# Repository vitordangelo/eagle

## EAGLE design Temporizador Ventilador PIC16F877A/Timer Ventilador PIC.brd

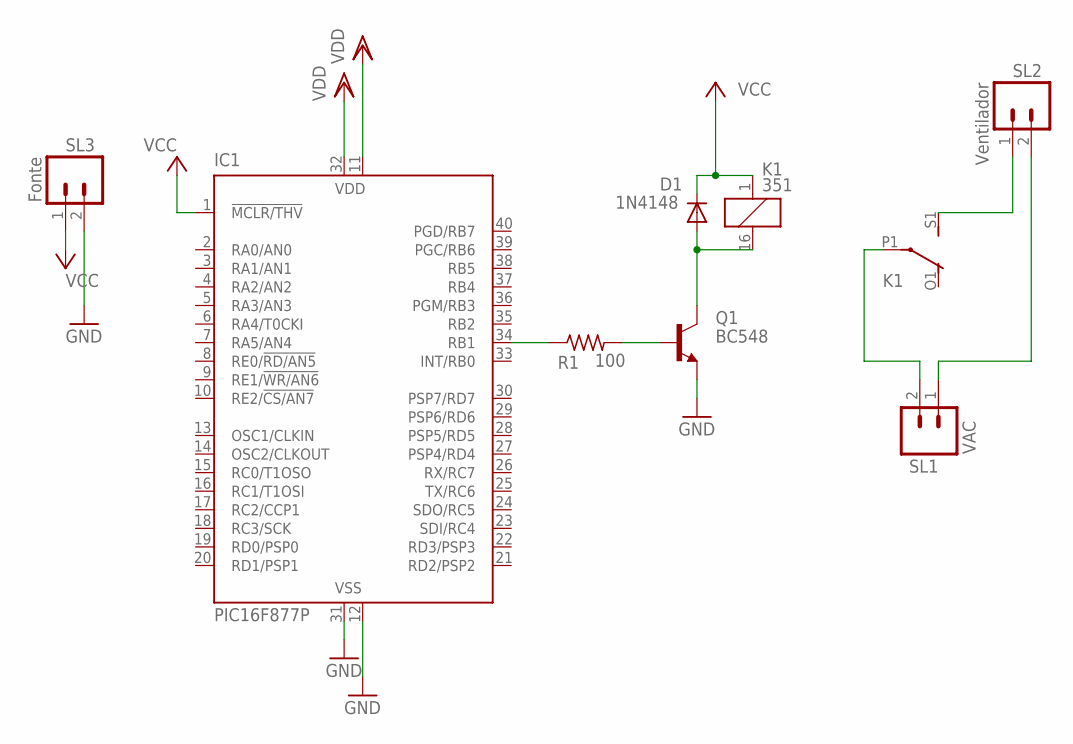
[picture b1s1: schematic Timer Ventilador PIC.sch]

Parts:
D1: 1N4148; DO35-7
IC1: PIC16F877P; DIL40
K1: 351
Q1: BC548; TO92-EBC
R1: 100; 0204/7
SL1: VAC; 02P
SL2: Ventilador; 02P
SL3: Fonte; 02P

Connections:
GND: IC1.12 (VSS), IC1.31 (VSS), Q1.E, SL3.2
unnamed: IC1.34 (RB1), R1.1
unnamed: Q1.B, R1.2
unnamed: K1.P1, SL1.2
unnamed: D1.A, K1.16 (2), Q1.C
unnamed: K1.S1 (S), SL2.1
unnamed: SL1.1, SL2.2
VCC: D1.C, IC1.1 (!MCLR/THV), K1.1, SL3.1
VDD: IC1.11 (VDD), IC1.32 (VDD)

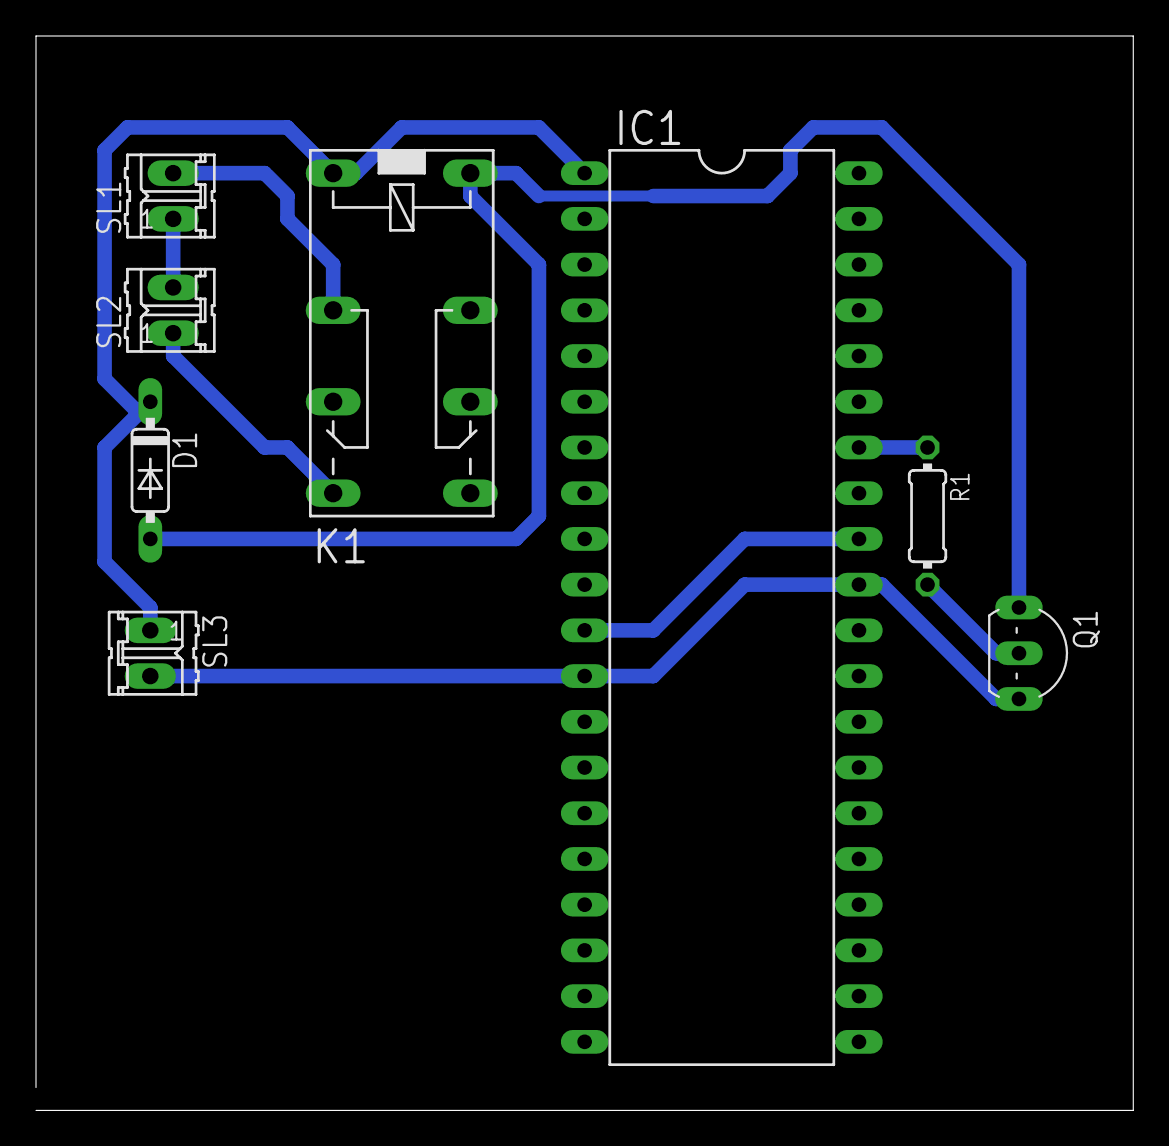
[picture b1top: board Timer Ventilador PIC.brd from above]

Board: 2 copper layers, 61.0 x 59.7 mm, 8 parts (0 on the bottom side), 9 nets.

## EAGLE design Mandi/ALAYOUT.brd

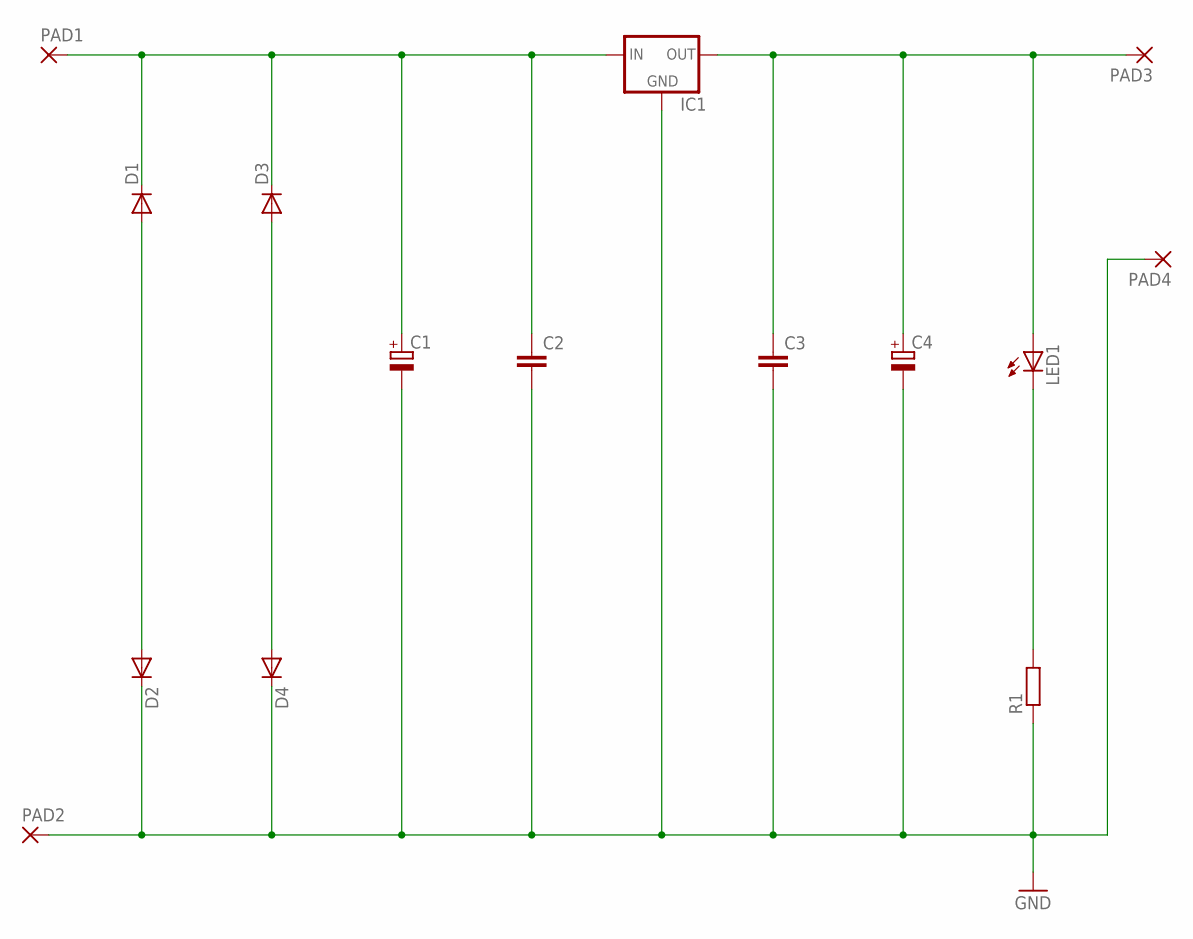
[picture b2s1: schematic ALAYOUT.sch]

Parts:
C1: CPOL-EUE7.5-16; E7,5-16
C2, C3: C-EU050-030X075; C050-030X075
C4: CPOL-EUE5-8.5; E5-8,5
D1, D2, D3, D4: DIODE-DO35-10; DO35-10
IC1: 78XXS
LED1: LED3MM
PAD1, PAD2, PAD3, PAD4: 3,17/1,1
R1: R-EU_0207/10; 0207/10

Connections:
GND: C1.-, C2.2, C3.2, C4.-, D2.C, D4.C, IC1.GND, PAD2.1, PAD4.1, R1.1
unnamed: D3.A, D4.A
unnamed: C1.+, C2.1, D1.C, D3.C, IC1.IN, PAD1.1
unnamed: D1.A, D2.A
unnamed: C3.1, C4.+, IC1.OUT, LED1.A, PAD3.1
unnamed: LED1.K (C), R1.2

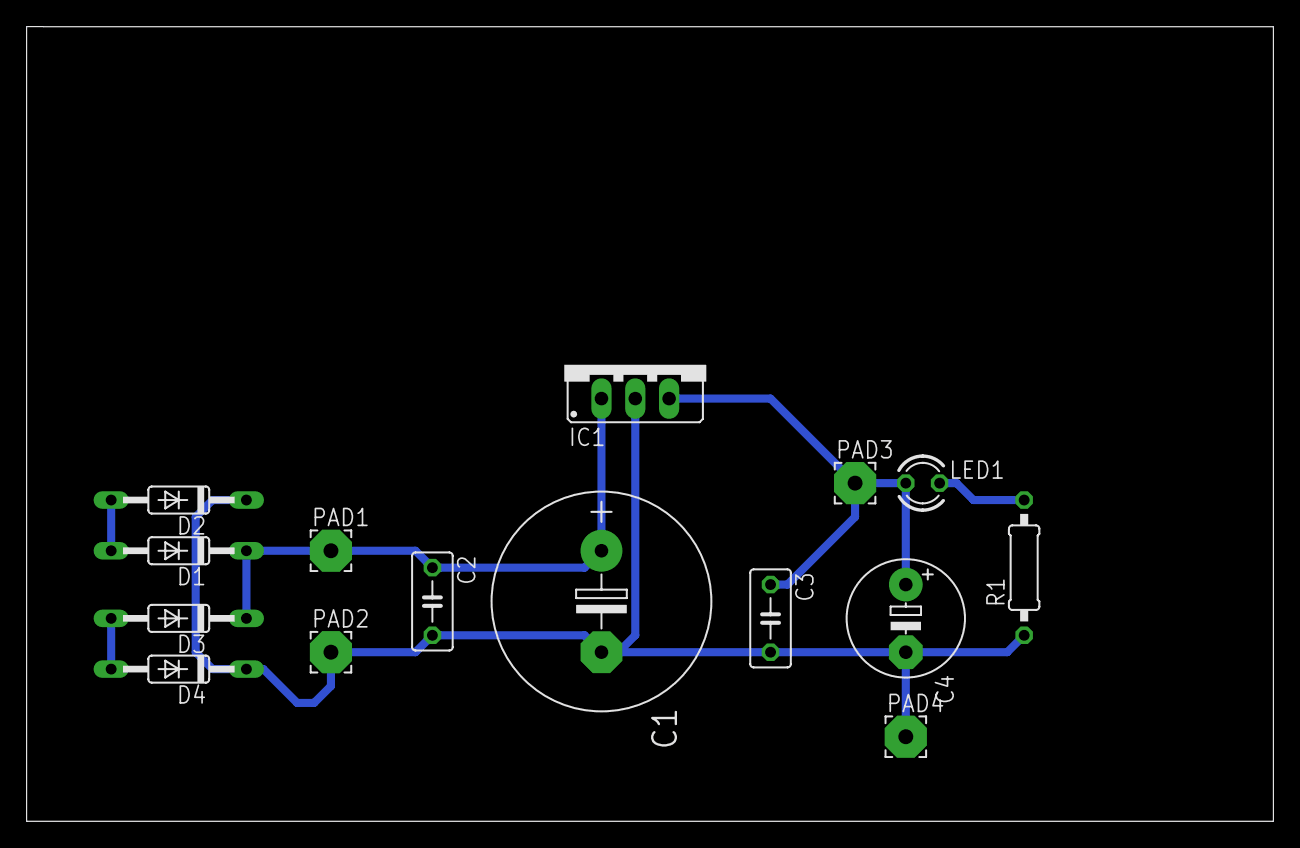
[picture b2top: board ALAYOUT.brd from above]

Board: 2 copper layers, 93.6 x 59.7 mm, 15 parts (0 on the bottom side), 6 nets.

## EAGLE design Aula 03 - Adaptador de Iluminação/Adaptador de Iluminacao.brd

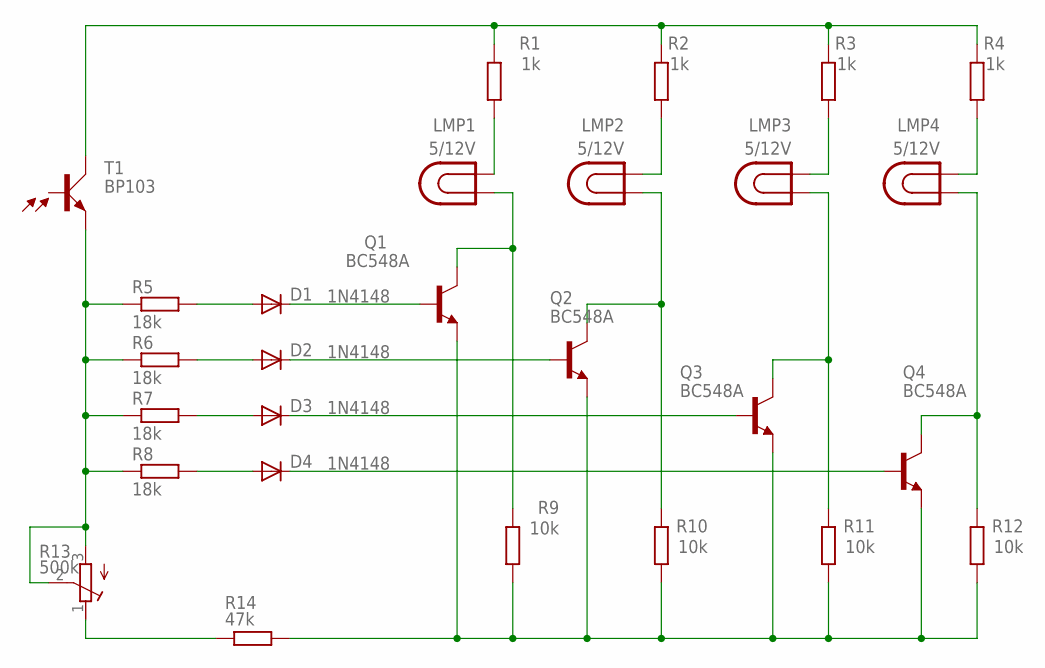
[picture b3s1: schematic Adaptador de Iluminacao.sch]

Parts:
D1, D2, D3, D4: 1N4148; DO35-7
LMP1, LMP2, LMP3, LMP4: 5/12V; LDH-5R
Q1, Q2, Q3, Q4: BC548A; TO92-EBC
R1, R2, R3, R4: 1k; 0207/10
R5, R6, R7, R8: 18k; 0207/10
R9, R10, R11, R12: 10k; 0207/10
R13: 500k; RTRIM43P
R14: 47k; 0207/10
T1: BP103

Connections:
unnamed: R5.1, R6.1, R7.1, R8.1, R13.2 (S), R13.3 (A), T1.E
unnamed: D1.A, R5.2
unnamed: D2.A, R6.2
unnamed: D3.A, R7.2
unnamed: D4.A, R8.2
unnamed: R13.1 (E), R14.1
unnamed: D1.C, Q1.B
unnamed: Q1.E, Q2.E, Q3.E, Q4.E, R9.1, R10.1, R11.1, R12.1, R14.2
unnamed: LMP1.1, Q1.C, R9.2
unnamed: LMP2.1, Q2.C, R10.2
unnamed: LMP1.2, R1.1
unnamed: R1.2, R2.2, R3.2, R4.2, T1.C
unnamed: LMP2.2, R2.1
unnamed: D4.C, Q4.B
unnamed: D2.C, Q2.B
unnamed: D3.C, Q3.B
unnamed: LMP3.1, Q3.C, R11.2
unnamed: LMP4.1, Q4.C, R12.2
unnamed: LMP3.2, R3.1
unnamed: LMP4.2, R4.1

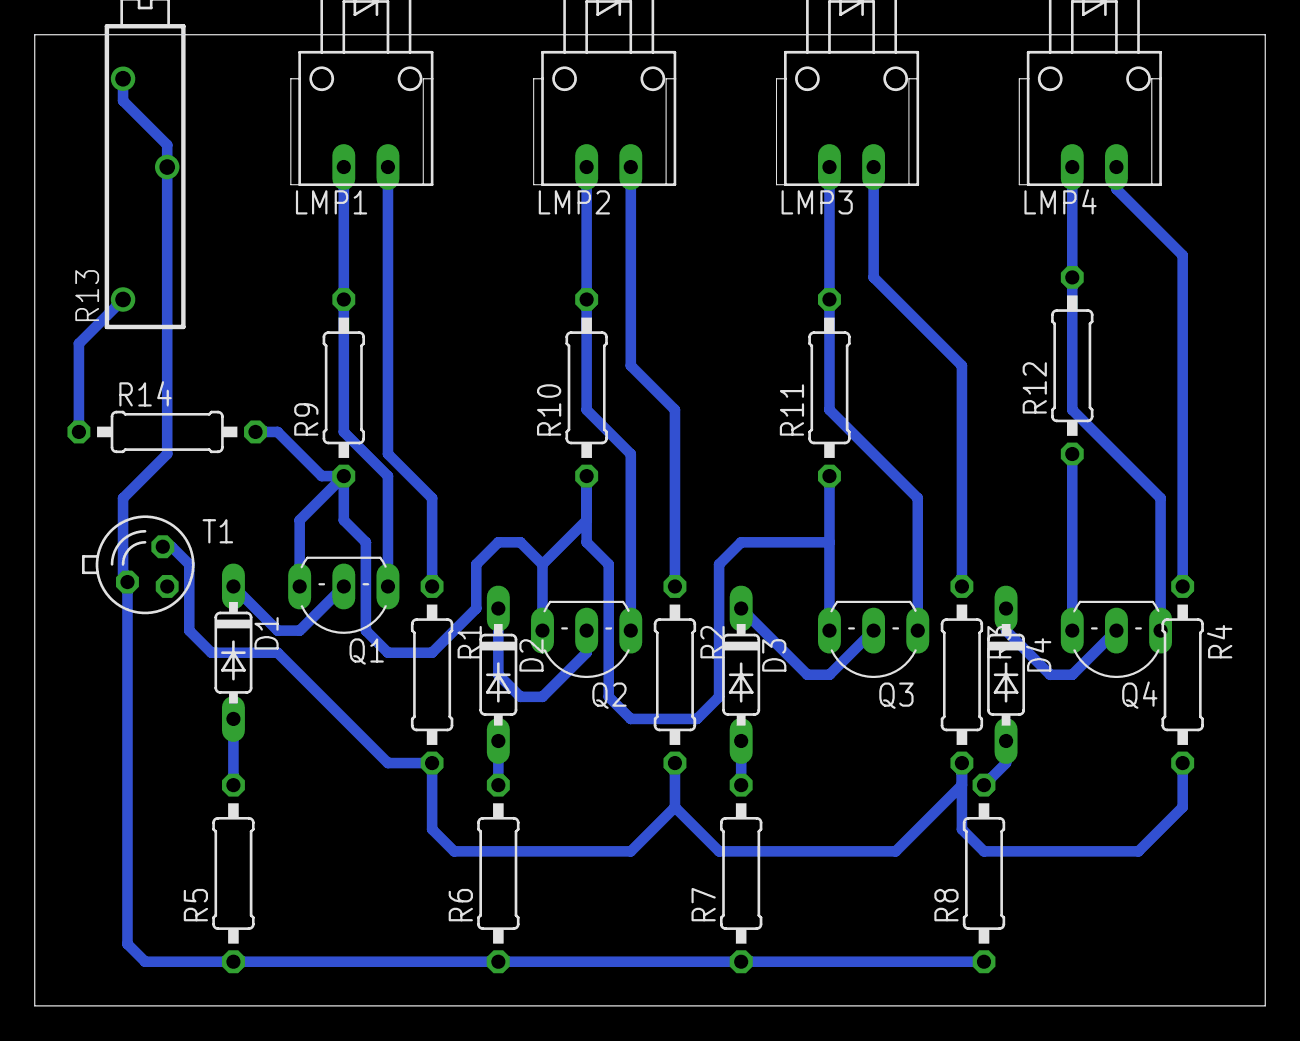
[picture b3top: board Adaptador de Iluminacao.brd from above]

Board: 2 copper layers, 70.8 x 55.9 mm, 27 parts (0 on the bottom side), 20 nets.

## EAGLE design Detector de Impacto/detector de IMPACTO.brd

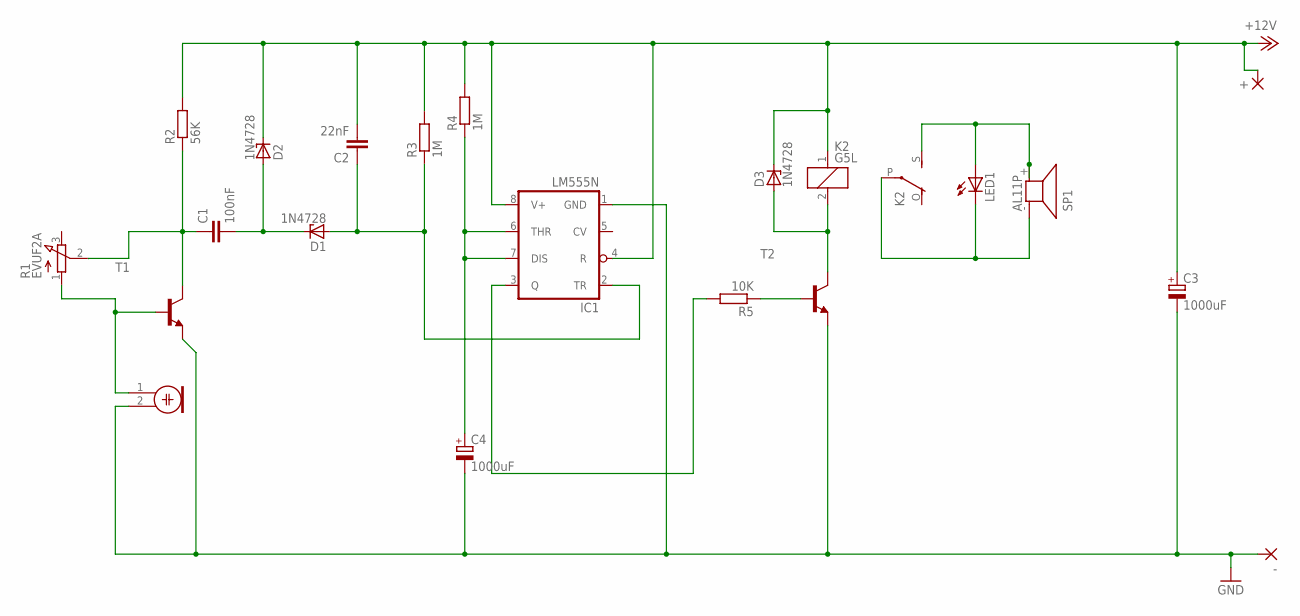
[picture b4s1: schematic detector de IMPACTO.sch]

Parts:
+: 1,6/0,8
-: 1,6/0,8
C1: 100nF; C025-024X044
C2: 22nF; C025-024X044
C3, C4: 1000uF; E5-8,5
D1, D2, D3: 1N4728; DO41Z10
IC1: LM555N; DIL08
K2: G5L; G5LE
LED1: LED3MM
M1: ELECTRET_MICROPHON-WM-64PC/64PK; WM-64PC/64PK
R1: EVUF2A; EVUF
R2: 56K; 0207/10
R3, R4: 1M; 0207/10
R5: 10K; 0207/10
SP1: AL11P
T1, T2: BC548-NPN-TO92-CBE; TO92-CBE

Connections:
+12V: +.1, C2.2, C3.+, D2.C, D3.C, IC1.4 (R), IC1.8 (V+), K2.1, R2.2, R3.2, R4.2
GND: -.1, C3.-, C4.-, IC1.1 (GND), M1.2, T1.E, T2.E
unnamed: C1.1, R1.2 (S), R2.1, T1.C
unnamed: M1.1, R1.1 (A), T1.B
unnamed: C1.2, D1.C, D2.A
unnamed: C2.1, D1.A, IC1.2 (TR), R3.1
unnamed: IC1.3 (Q), R5.2
unnamed: K2.S, LED1.A, SP1.+ (2)
unnamed: C4.+, IC1.6 (THR), IC1.7 (DIS), R4.1
unnamed: R5.1, T2.B
unnamed: D3.A, K2.2, T2.C
unnamed: K2.P, LED1.K (C), SP1.- (1)

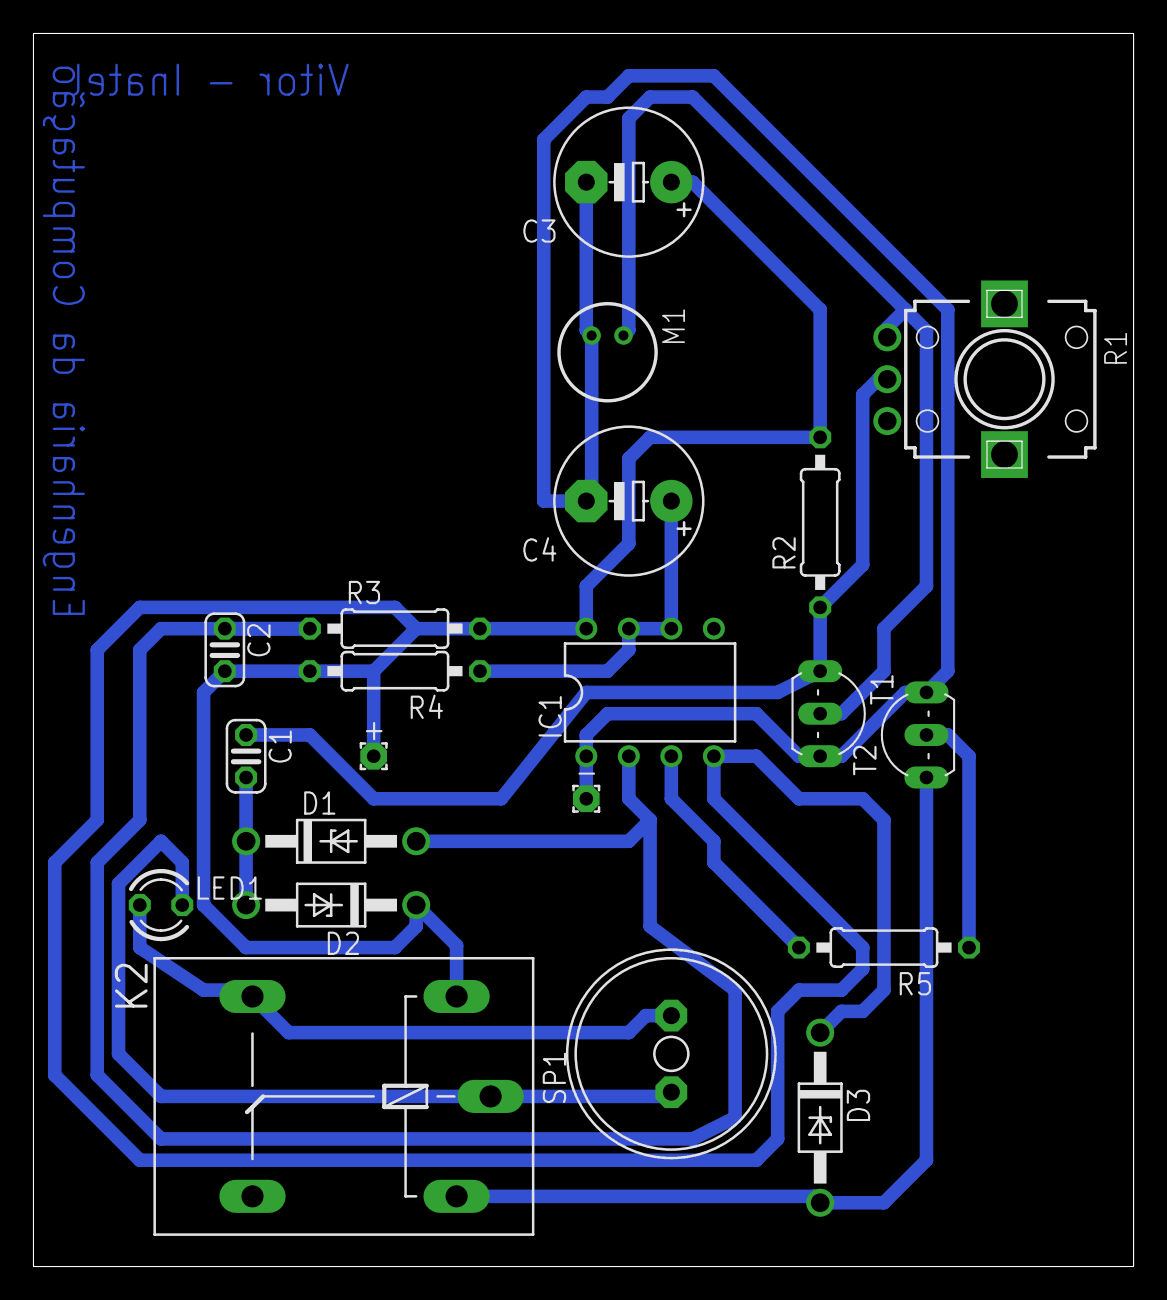
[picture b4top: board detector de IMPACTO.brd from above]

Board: 2 copper layers, 65.7 x 73.7 mm, 21 parts (0 on the bottom side), 12 nets.

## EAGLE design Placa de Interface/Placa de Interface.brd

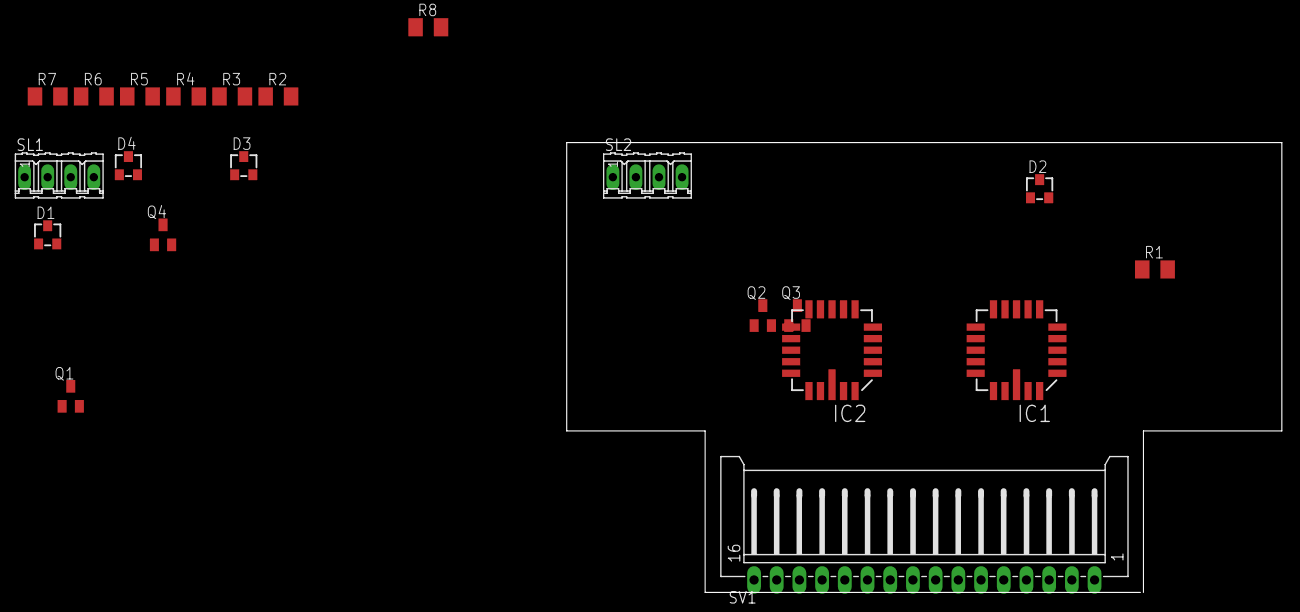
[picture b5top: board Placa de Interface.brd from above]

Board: 2 copper layers, 78.7 x 49.5 mm, 21 parts (0 on the bottom side), 31 nets, no tracks yet.

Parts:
D1, D2, D3, D4: BZX84CSMD; TO236
IC1, IC2: 74ACT02FK; LCC20
Q1, Q2, Q3, Q4: BCF29SMD; SOT23-BEC
R1, R3, R5, R7: 10k; M1206
R2, R4, R6, R8: 1k; M1206
SL1, SL2: 04P
SV1: L16P

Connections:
+12V: D1.C, D2.C, D3.C, D4.C, SL1.1, SL1.2, SL2.1, SL2.2
GND: IC1.10, IC2.10, Q1.E, Q2.E, Q3.E, Q4.E, R2.1, R4.1, R6.1, R8.1
unnamed: Q1.B, R1.2, R2.2
unnamed: D1.A, Q1.C, SL1.4
unnamed: Q2.B, R3.2, R4.2
unnamed: D2.A, Q2.C, SL1.3
unnamed: IC1.2, IC1.6, R1.1
unnamed: IC1.14, IC1.19, R3.1
unnamed: Q3.B, R5.2, R6.2
unnamed: D3.A, Q3.C, SL2.4
unnamed: Q4.B, R7.2, R8.2
unnamed: D4.A, Q4.C, SL2.3
unnamed: IC2.14, IC2.19, R7.1
unnamed: IC2.2, IC2.6, R5.1
unnamed: IC1.3, SV1.1
unnamed: IC1.4, SV1.2
unnamed: IC1.8, SV1.3
unnamed: IC1.9, SV1.4
unnamed: IC1.12, SV1.5
unnamed: IC1.13, SV1.6
unnamed: IC1.16, SV1.7
unnamed: IC1.18, SV1.8
unnamed: IC2.18, SV1.16
unnamed: IC2.16, SV1.15
unnamed: IC2.13, SV1.14
unnamed: IC2.12, SV1.13
unnamed: IC2.9, SV1.12
unnamed: IC2.8, SV1.11
unnamed: IC2.4, SV1.10
unnamed: IC2.3, SV1.9
VCC: IC1.20, IC2.20

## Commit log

2015-02-01 Projetos até 2014
